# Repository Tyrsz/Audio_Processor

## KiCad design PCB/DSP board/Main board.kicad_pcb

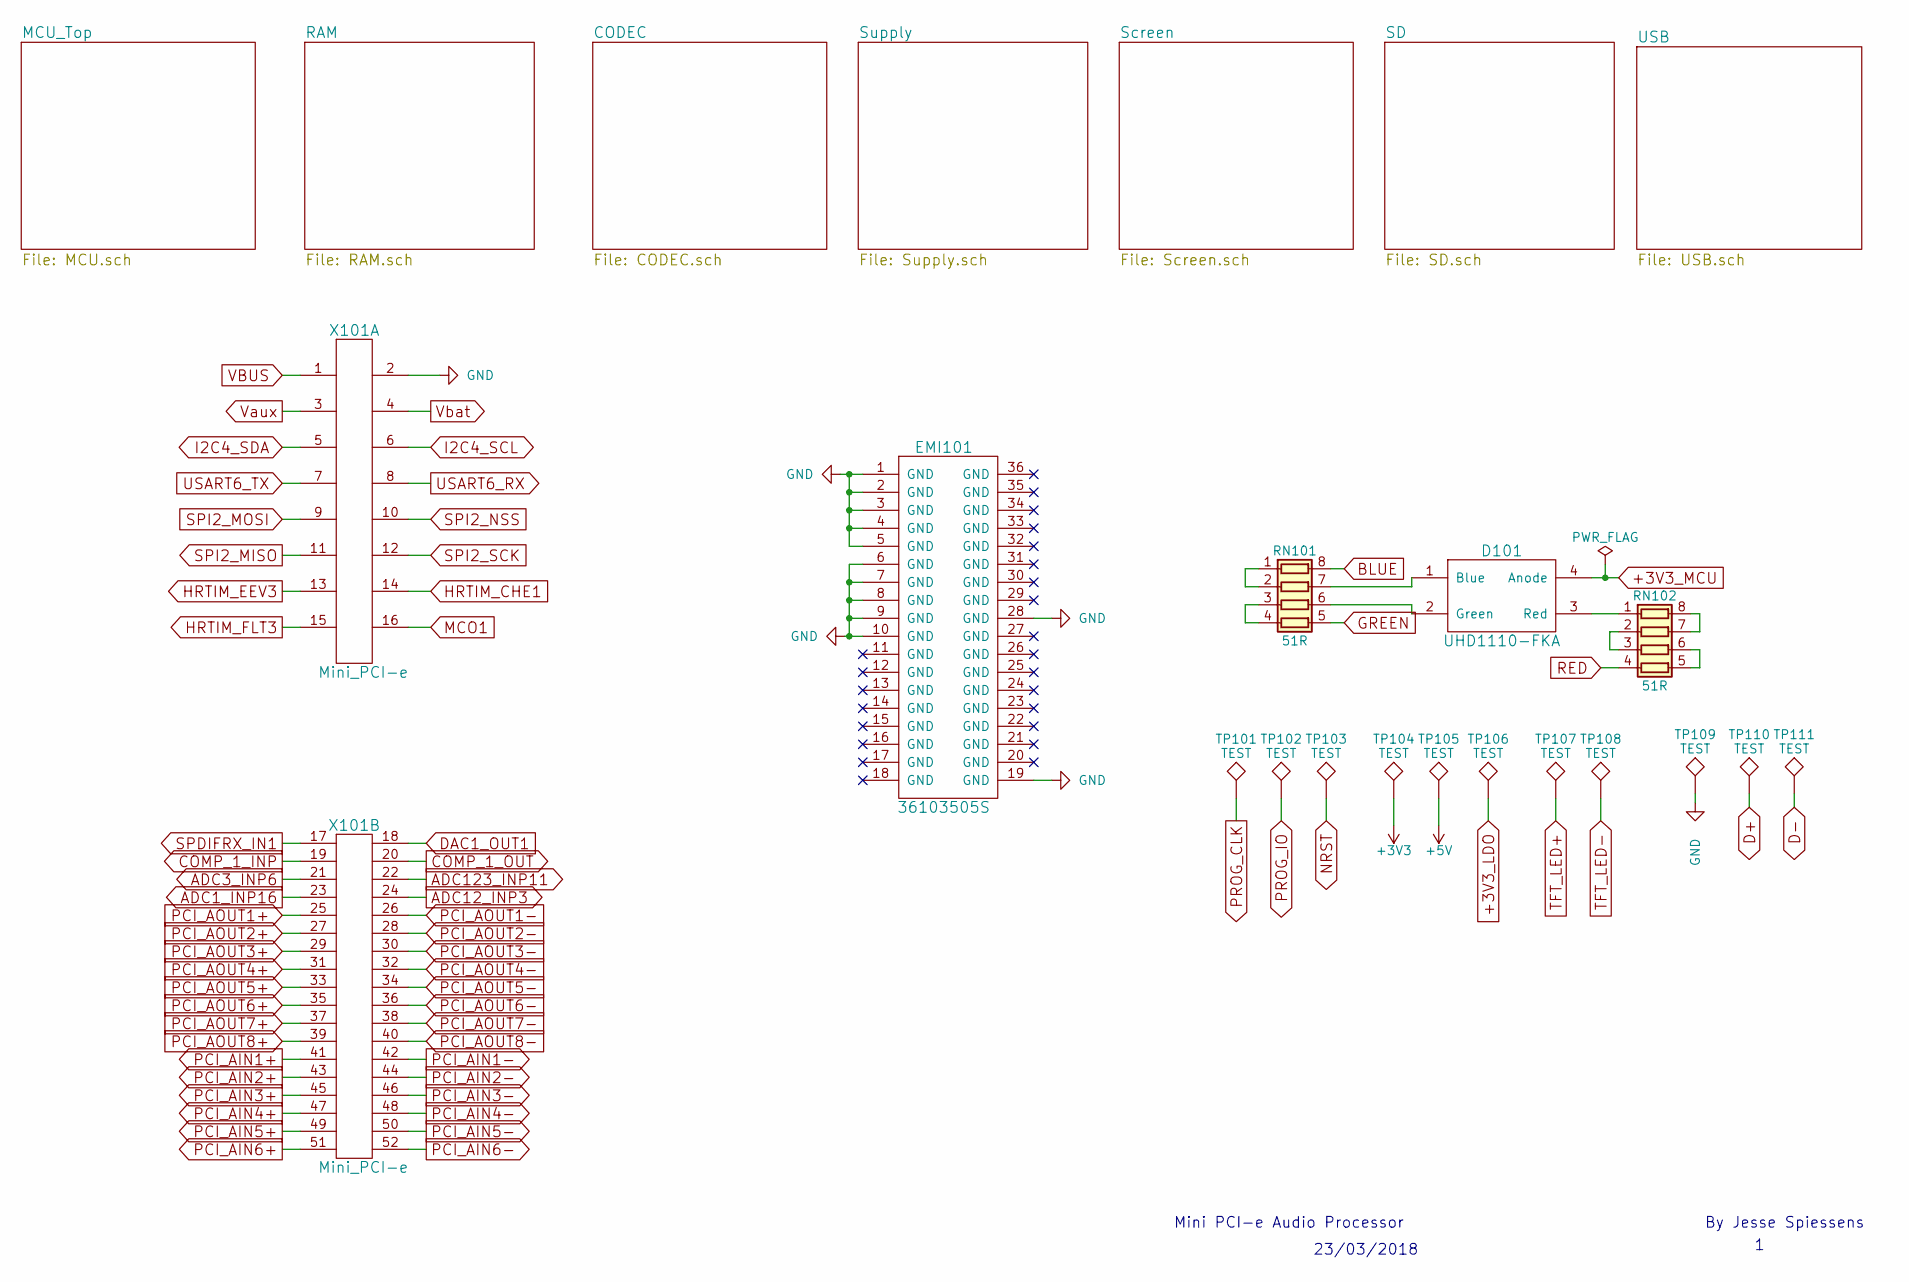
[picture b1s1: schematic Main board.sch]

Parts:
D101: UHD1110-FKA; PLCC-4_1x1mm
EMI101: 36103505S
RN101, RN102: 51R; 0603_RN4
TP101, TP102, TP103, TP104, TP105, TP106, TP107, TP108, TP109, TP110, TP111: TEST; Measurement_Point_Round-SMD-Pad_Small
X101: Mini_PCI-e

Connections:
+3V3: TP104.1; also elsewhere on the board
+3V3_LDO: TP106.1; also elsewhere on the board
+3V3_MCU: D101.4 (Anode); also elsewhere on the board
+5V: TP105.1; also elsewhere on the board
ADC1_INP16: X101.23; also elsewhere on the board
ADC3_INP6: X101.21; also elsewhere on the board
ADC12_INP3: X101.24; also elsewhere on the board
ADC123_INP11: X101.22; also elsewhere on the board
BLUE: RN101.8 (R1.2); also elsewhere on the board
COMP_1_INP: X101.19; also elsewhere on the board
COMP_1_OUT: X101.20; also elsewhere on the board
D+: TP110.1; also elsewhere on the board
D-: TP111.1; also elsewhere on the board
DAC1_OUT1: X101.18; also elsewhere on the board
GND: EMI101.1, EMI101.2, EMI101.3, EMI101.4, EMI101.5, EMI101.6, EMI101.7, EMI101.8, EMI101.9, EMI101.10, EMI101.19, EMI101.28, TP109.1, X101.2; also elsewhere on the board
GREEN: RN101.5 (R4.2); also elsewhere on the board
HRTIM_CHE1: X101.14; also elsewhere on the board
HRTIM_EEV3: X101.13; also elsewhere on the board
HRTIM_FLT3: X101.15; also elsewhere on the board
I2C4_SCL: X101.6; also elsewhere on the board
I2C4_SDA: X101.5; also elsewhere on the board
MCO1: X101.16; also elsewhere on the board
NRST: TP103.1; also elsewhere on the board
unnamed: D101.1 (Blue), RN101.7 (R2.2)
unnamed: D101.2 (Green), RN101.6 (R3.2)
unnamed: D101.3 (Red), RN102.1 (R1.1)
unnamed: RN101.1 (R1.1), RN101.2 (R2.1)
unnamed: RN101.3 (R3.1), RN101.4 (R4.1)
unnamed: RN102.2 (R2.1), RN102.3 (R3.1)
unnamed: RN102.5 (R4.2), RN102.6 (R3.2)
unnamed: RN102.7 (R2.2), RN102.8 (R1.2)
PCI_AIN1+: X101.41; also elsewhere on the board
PCI_AIN1-: X101.42; also elsewhere on the board
PCI_AIN2+: X101.43; also elsewhere on the board
PCI_AIN2-: X101.44; also elsewhere on the board
PCI_AIN3+: X101.45; also elsewhere on the board
PCI_AIN3-: X101.46; also elsewhere on the board
PCI_AIN4+: X101.47; also elsewhere on the board
PCI_AIN4-: X101.48; also elsewhere on the board
PCI_AIN5+: X101.49; also elsewhere on the board
PCI_AIN5-: X101.50; also elsewhere on the board
PCI_AIN6+: X101.51; also elsewhere on the board
PCI_AIN6-: X101.52; also elsewhere on the board
PCI_AOUT1+: X101.25; also elsewhere on the board
PCI_AOUT1-: X101.26; also elsewhere on the board
PCI_AOUT2+: X101.27; also elsewhere on the board
PCI_AOUT2-: X101.28; also elsewhere on the board
PCI_AOUT3+: X101.29; also elsewhere on the board
PCI_AOUT3-: X101.30; also elsewhere on the board
PCI_AOUT4+: X101.31; also elsewhere on the board
PCI_AOUT4-: X101.32; also elsewhere on the board
PCI_AOUT5+: X101.33; also elsewhere on the board
PCI_AOUT5-: X101.34; also elsewhere on the board
PCI_AOUT6+: X101.35; also elsewhere on the board
PCI_AOUT6-: X101.36; also elsewhere on the board
PCI_AOUT7+: X101.37; also elsewhere on the board
PCI_AOUT7-: X101.38; also elsewhere on the board
PCI_AOUT8+: X101.39; also elsewhere on the board
PCI_AOUT8-: X101.40; also elsewhere on the board
PROG_CLK: TP101.1; also elsewhere on the board
PROG_IO: TP102.1; also elsewhere on the board
RED: RN102.4 (R4.1); also elsewhere on the board
SPDIFRX_IN1: X101.17; also elsewhere on the board
SPI2_MISO: X101.11; also elsewhere on the board
SPI2_MOSI: X101.9; also elsewhere on the board
SPI2_NSS: X101.10; also elsewhere on the board
SPI2_SCK: X101.12; also elsewhere on the board
TFT_LED+: TP107.1; also elsewhere on the board
TFT_LED-: TP108.1; also elsewhere on the board
USART6_RX: X101.8; also elsewhere on the board
USART6_TX: X101.7; also elsewhere on the board
VBUS: X101.1; also elsewhere on the board
Vaux: X101.3; also elsewhere on the board
Vbat: X101.4; also elsewhere on the board

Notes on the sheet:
23/03/2018
Mini PCI-e Audio Processor
By Jesse Spiessens

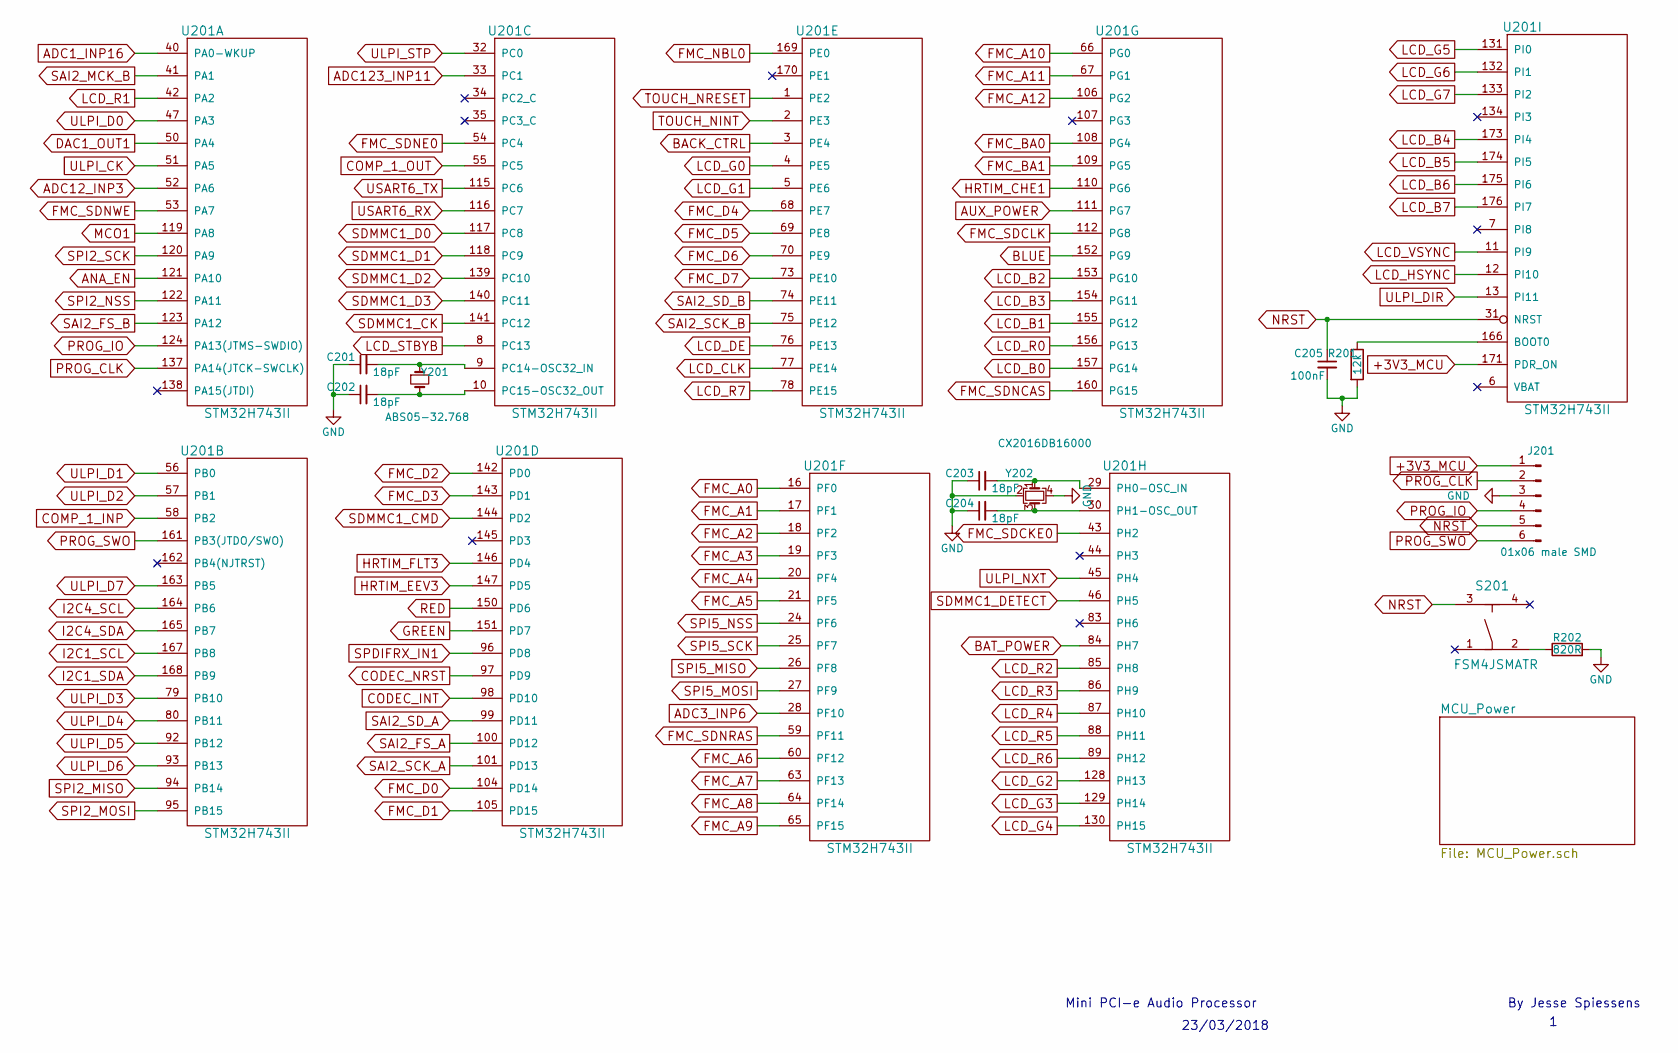
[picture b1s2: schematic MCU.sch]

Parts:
C201, C202, C203, C204: 18pF; C_0603
C205: 100nF; C_0603
J201: 01x06 male SMD; Pin_Header_Straight_1x06_Pitch2.54mm_SMD_Pin1Right
R201: 12k; R_0603
R202: 820R; R_0603
S201: FSM4JSMATR
U201: STM32H743II; LQFP-176_24x24mm_Pitch0.5mm
Y201: ABS05-32.768; Crystal_SMD_MicroCrystal_CM9V-T1A-2pin_1.6x1.0mm
Y202: CX2016DB16000; Crystal_SMD_2016-4pin_2.0x1.6mm

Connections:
+3V3_MCU: J201.1, U201.171 (PDR_ON); also elsewhere on the board
ADC1_INP16: U201.40 (PA0-WKUP); also elsewhere on the board
ADC3_INP6: U201.28 (PF10); also elsewhere on the board
ADC12_INP3: U201.52 (PA6); also elsewhere on the board
ADC123_INP11: U201.33 (PC1); also elsewhere on the board
ANA_EN: U201.121 (PA10); also elsewhere on the board
AUX_POWER: U201.111 (PG7); also elsewhere on the board
BACK_CTRL: U201.3 (PE4); also elsewhere on the board
BAT_POWER: U201.84 (PH7); also elsewhere on the board
BLUE: U201.152 (PG9); also elsewhere on the board
CODEC_INT: U201.98 (PD10); also elsewhere on the board
CODEC_NRST: U201.97 (PD9); also elsewhere on the board
COMP_1_INP: U201.58 (PB2); also elsewhere on the board
COMP_1_OUT: U201.55 (PC5); also elsewhere on the board
DAC1_OUT1: U201.50 (PA4); also elsewhere on the board
FMC_A0: U201.16 (PF0); also elsewhere on the board
FMC_A1: U201.17 (PF1); also elsewhere on the board
FMC_A2: U201.18 (PF2); also elsewhere on the board
FMC_A3: U201.19 (PF3); also elsewhere on the board
FMC_A4: U201.20 (PF4); also elsewhere on the board
FMC_A5: U201.21 (PF5); also elsewhere on the board
FMC_A6: U201.60 (PF12); also elsewhere on the board
FMC_A7: U201.63 (PF13); also elsewhere on the board
FMC_A8: U201.64 (PF14); also elsewhere on the board
FMC_A9: U201.65 (PF15); also elsewhere on the board
FMC_A10: U201.66 (PG0); also elsewhere on the board
FMC_A11: U201.67 (PG1); also elsewhere on the board
FMC_A12: U201.106 (PG2); also elsewhere on the board
FMC_BA0: U201.108 (PG4); also elsewhere on the board
FMC_BA1: U201.109 (PG5); also elsewhere on the board
FMC_D0: U201.104 (PD14); also elsewhere on the board
FMC_D1: U201.105 (PD15); also elsewhere on the board
FMC_D2: U201.142 (PD0); also elsewhere on the board
FMC_D3: U201.143 (PD1); also elsewhere on the board
FMC_D4: U201.68 (PE7); also elsewhere on the board
FMC_D5: U201.69 (PE8); also elsewhere on the board
FMC_D6: U201.70 (PE9); also elsewhere on the board
FMC_D7: U201.73 (PE10); also elsewhere on the board
FMC_NBL0: U201.169 (PE0); also elsewhere on the board
FMC_SDCKE0: U201.43 (PH2); also elsewhere on the board
FMC_SDCLK: U201.112 (PG8); also elsewhere on the board
FMC_SDNCAS: U201.160 (PG15); also elsewhere on the board
FMC_SDNE0: U201.54 (PC4); also elsewhere on the board
FMC_SDNRAS: U201.59 (PF11); also elsewhere on the board
FMC_SDNWE: U201.53 (PA7); also elsewhere on the board
GND: C201.1, C202.1, C203.1, C204.1, C205.2, J201.3, R201.2, R202.2, Y202.2, Y202.4; also elsewhere on the board
GREEN: U201.151 (PD7); also elsewhere on the board
HRTIM_CHE1: U201.110 (PG6); also elsewhere on the board
HRTIM_EEV3: U201.147 (PD5); also elsewhere on the board
HRTIM_FLT3: U201.146 (PD4); also elsewhere on the board
I2C1_SCL: U201.167 (PB8); also elsewhere on the board
I2C1_SDA: U201.168 (PB9); also elsewhere on the board
I2C4_SCL: U201.164 (PB6); also elsewhere on the board
I2C4_SDA: U201.165 (PB7); also elsewhere on the board
LCD_B0: U201.157 (PG14); also elsewhere on the board
LCD_B1: U201.155 (PG12); also elsewhere on the board
LCD_B2: U201.153 (PG10); also elsewhere on the board
LCD_B3: U201.154 (PG11); also elsewhere on the board
LCD_B4: U201.173 (PI4); also elsewhere on the board
LCD_B5: U201.174 (PI5); also elsewhere on the board
LCD_B6: U201.175 (PI6); also elsewhere on the board
LCD_B7: U201.176 (PI7); also elsewhere on the board
LCD_CLK: U201.77 (PE14); also elsewhere on the board
LCD_DE: U201.76 (PE13); also elsewhere on the board
LCD_G0: U201.4 (PE5); also elsewhere on the board
LCD_G1: U201.5 (PE6); also elsewhere on the board
LCD_G2: U201.128 (PH13); also elsewhere on the board
LCD_G3: U201.129 (PH14); also elsewhere on the board
LCD_G4: U201.130 (PH15); also elsewhere on the board
LCD_G5: U201.131 (PI0); also elsewhere on the board
LCD_G6: U201.132 (PI1); also elsewhere on the board
LCD_G7: U201.133 (PI2); also elsewhere on the board
LCD_HSYNC: U201.12 (PI10); also elsewhere on the board
LCD_R0: U201.156 (PG13); also elsewhere on the board
LCD_R1: U201.42 (PA2); also elsewhere on the board
LCD_R2: U201.85 (PH8); also elsewhere on the board
LCD_R3: U201.86 (PH9); also elsewhere on the board
LCD_R4: U201.87 (PH10); also elsewhere on the board
LCD_R5: U201.88 (PH11); also elsewhere on the board
LCD_R6: U201.89 (PH12); also elsewhere on the board
LCD_R7: U201.78 (PE15); also elsewhere on the board
LCD_STBYB: U201.8 (PC13); also elsewhere on the board
LCD_VSYNC: U201.11 (PI9); also elsewhere on the board
MCO1: U201.119 (PA8); also elsewhere on the board
NRST: C205.1, J201.5, S201.3, U201.31 (NRST); also elsewhere on the board
unnamed: C201.2, U201.9 (PC14-OSC32_IN), Y201.1
unnamed: C202.2, U201.10 (PC15-OSC32_OUT), Y201.2
unnamed: C203.2, U201.29 (PH0-OSC_IN), Y202.1
unnamed: C204.2, U201.30 (PH1-OSC_OUT), Y202.3
unnamed: R201.1, U201.166 (BOOT0)
unnamed: R202.1, S201.2
PROG_CLK: J201.2, U201.137 (PA14(JTCK-SWCLK)); also elsewhere on the board
PROG_IO: J201.4, U201.124 (PA13(JTMS-SWDIO)); also elsewhere on the board
PROG_SWO: J201.6, U201.161 (PB3(JTDO/SWO))
RED: U201.150 (PD6); also elsewhere on the board
SAI2_FS_A: U201.100 (PD12); also elsewhere on the board
SAI2_FS_B: U201.123 (PA12); also elsewhere on the board
SAI2_MCK_B: U201.41 (PA1); also elsewhere on the board
SAI2_SCK_A: U201.101 (PD13); also elsewhere on the board
SAI2_SCK_B: U201.75 (PE12); also elsewhere on the board
SAI2_SD_A: U201.99 (PD11); also elsewhere on the board
SAI2_SD_B: U201.74 (PE11); also elsewhere on the board
SDMMC1_CK: U201.141 (PC12); also elsewhere on the board
SDMMC1_CMD: U201.144 (PD2); also elsewhere on the board
SDMMC1_D0: U201.117 (PC8); also elsewhere on the board
SDMMC1_D1: U201.118 (PC9); also elsewhere on the board
SDMMC1_D2: U201.139 (PC10); also elsewhere on the board
SDMMC1_D3: U201.140 (PC11); also elsewhere on the board
SDMMC1_DETECT: U201.46 (PH5); also elsewhere on the board
SPDIFRX_IN1: U201.96 (PD8); also elsewhere on the board
SPI2_MISO: U201.94 (PB14); also elsewhere on the board
SPI2_MOSI: U201.95 (PB15); also elsewhere on the board
SPI2_NSS: U201.122 (PA11); also elsewhere on the board
SPI2_SCK: U201.120 (PA9); also elsewhere on the board
SPI5_MISO: U201.26 (PF8); also elsewhere on the board
SPI5_MOSI: U201.27 (PF9); also elsewhere on the board
SPI5_NSS: U201.24 (PF6); also elsewhere on the board
SPI5_SCK: U201.25 (PF7); also elsewhere on the board
TOUCH_NINT: U201.2 (PE3); also elsewhere on the board
TOUCH_NRESET: U201.1 (PE2); also elsewhere on the board
ULPI_CK: U201.51 (PA5); also elsewhere on the board
ULPI_D0: U201.47 (PA3); also elsewhere on the board
ULPI_D1: U201.56 (PB0); also elsewhere on the board
ULPI_D2: U201.57 (PB1); also elsewhere on the board
ULPI_D3: U201.79 (PB10); also elsewhere on the board
ULPI_D4: U201.80 (PB11); also elsewhere on the board
ULPI_D5: U201.92 (PB12); also elsewhere on the board
ULPI_D6: U201.93 (PB13); also elsewhere on the board
ULPI_D7: U201.163 (PB5); also elsewhere on the board
ULPI_DIR: U201.13 (PI11); also elsewhere on the board
ULPI_NXT: U201.45 (PH4); also elsewhere on the board
ULPI_STP: U201.32 (PC0); also elsewhere on the board
USART6_RX: U201.116 (PC7); also elsewhere on the board
USART6_TX: U201.115 (PC6); also elsewhere on the board

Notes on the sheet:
23/03/2018
Mini PCI-e Audio Processor
By Jesse Spiessens

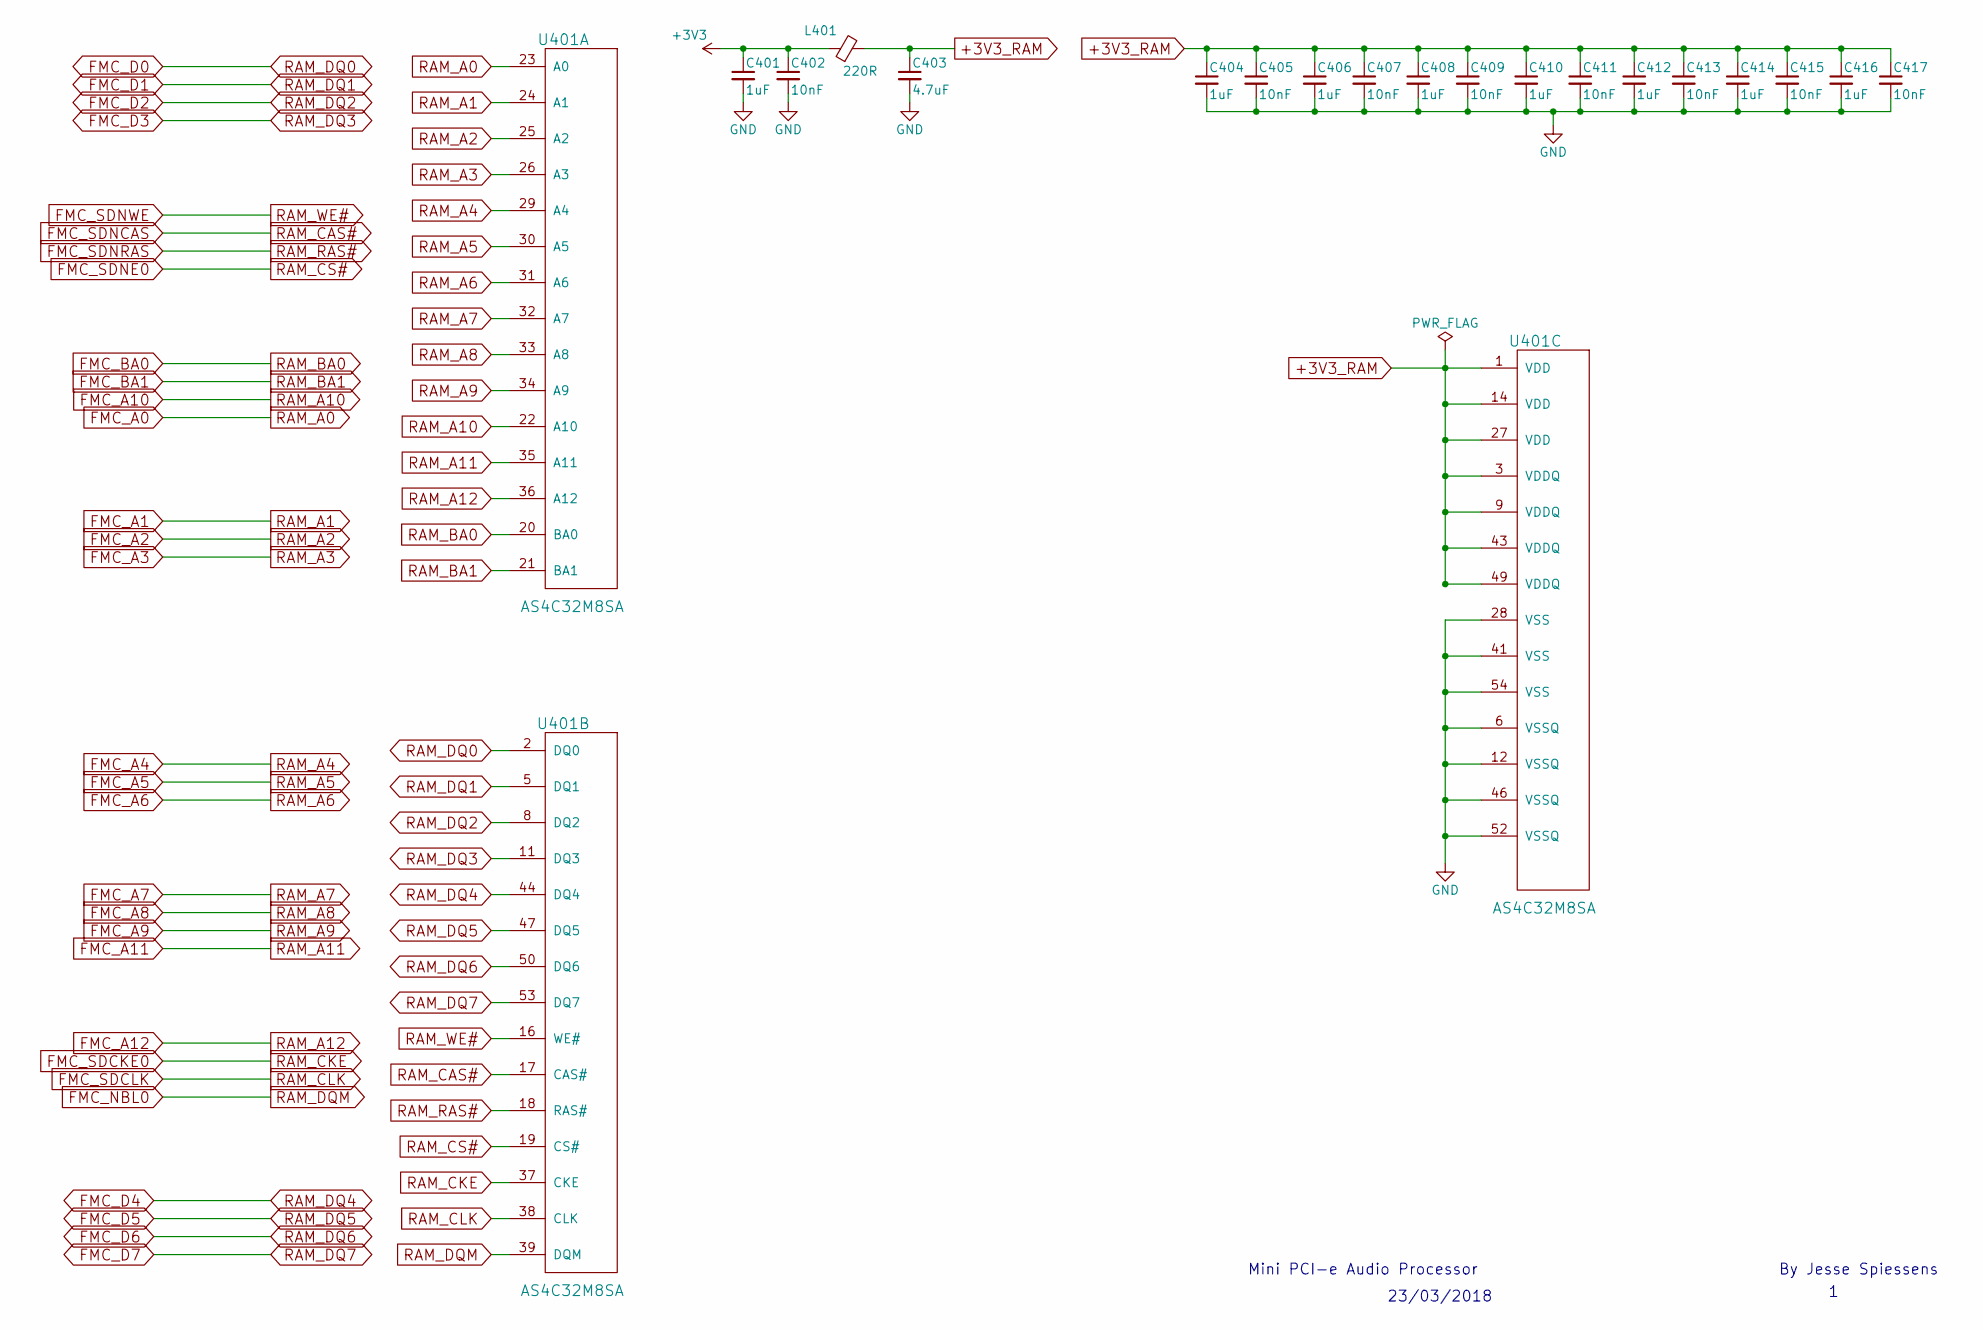
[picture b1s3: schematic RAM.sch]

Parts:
C401, C404, C406, C408, C410, C412, C414, C416: 1uF; C_0603
C402, C405, C407, C409, C411, C413, C415, C417: 10nF; C_0603
C403: 4.7uF; C_0805
L401: 220R; L_0603
U401: AS4C32M8SA; TSSOP-54_P-0.8mm

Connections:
+3V3: C401.1, C402.1, L401.1; also elsewhere on the board
+3V3_RAM: C403.1, C404.1, C405.1, C406.1, C407.1, C408.1, C409.1, C410.1, C411.1, C412.1, C413.1, C414.1, C415.1, C416.1, C417.1, L401.2, U401.1 (VDD), U401.3 (VDDQ), U401.9 (VDDQ), U401.14 (VDD), U401.27 (VDD), U401.43 (VDDQ), U401.49 (VDDQ)
FMC_A0: U401.23 (A0); also elsewhere on the board
FMC_A1: U401.24 (A1); also elsewhere on the board
FMC_A2: U401.25 (A2); also elsewhere on the board
FMC_A3: U401.26 (A3); also elsewhere on the board
FMC_A4: U401.29 (A4); also elsewhere on the board
FMC_A5: U401.30 (A5); also elsewhere on the board
FMC_A6: U401.31 (A6); also elsewhere on the board
FMC_A7: U401.32 (A7); also elsewhere on the board
FMC_A8: U401.33 (A8); also elsewhere on the board
FMC_A9: U401.34 (A9); also elsewhere on the board
FMC_A10: U401.22 (A10); also elsewhere on the board
FMC_A11: U401.35 (A11); also elsewhere on the board
FMC_A12: U401.36 (A12); also elsewhere on the board
FMC_BA0: U401.20 (BA0); also elsewhere on the board
FMC_BA1: U401.21 (BA1); also elsewhere on the board
FMC_D0: U401.2 (DQ0); also elsewhere on the board
FMC_D1: U401.5 (DQ1); also elsewhere on the board
FMC_D2: U401.8 (DQ2); also elsewhere on the board
FMC_D3: U401.11 (DQ3); also elsewhere on the board
FMC_D4: U401.44 (DQ4); also elsewhere on the board
FMC_D5: U401.47 (DQ5); also elsewhere on the board
FMC_D6: U401.50 (DQ6); also elsewhere on the board
FMC_D7: U401.53 (DQ7); also elsewhere on the board
FMC_NBL0: U401.39 (DQM); also elsewhere on the board
FMC_SDCKE0: U401.37 (CKE); also elsewhere on the board
FMC_SDCLK: U401.38 (CLK); also elsewhere on the board
FMC_SDNCAS: U401.17 (CAS#); also elsewhere on the board
FMC_SDNE0: U401.19 (CS#); also elsewhere on the board
FMC_SDNRAS: U401.18 (RAS#); also elsewhere on the board
FMC_SDNWE: U401.16 (WE#); also elsewhere on the board
GND: C401.2, C402.2, C403.2, C404.2, C405.2, C406.2, C407.2, C408.2, C409.2, C410.2, C411.2, C412.2, C413.2, C414.2, C415.2, C416.2, C417.2, U401.6 (VSSQ), U401.12 (VSSQ), U401.28 (VSS), U401.41 (VSS), U401.46 (VSSQ), U401.52 (VSSQ), U401.54 (VSS); also elsewhere on the board

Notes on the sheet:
23/03/2018
Mini PCI-e Audio Processor
By Jesse Spiessens

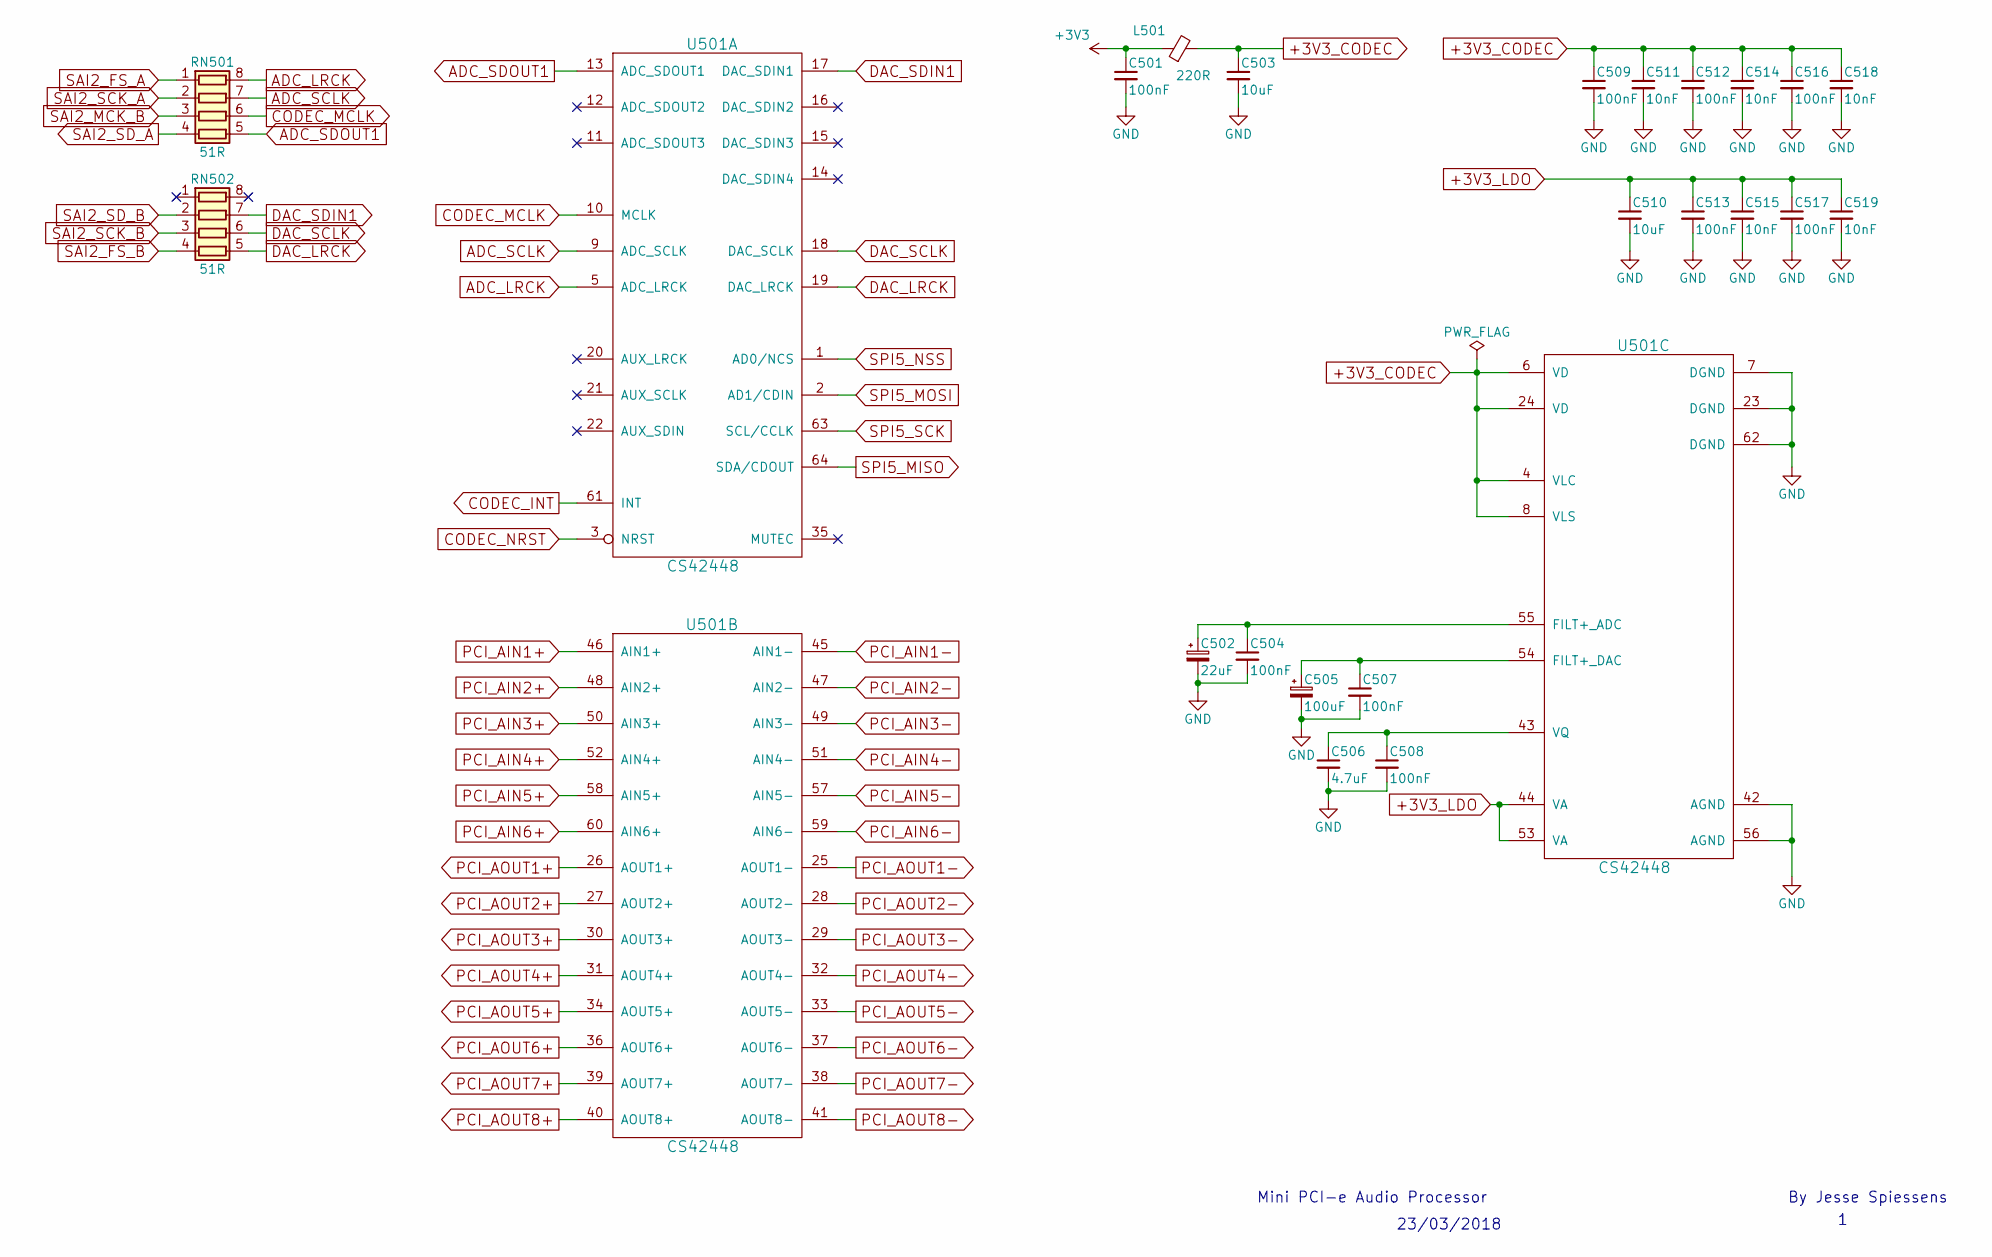
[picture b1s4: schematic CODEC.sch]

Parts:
C501, C504, C507, C508, C509, C512, C513, C516, C517: 100nF; C_0603
C502: 22uF; CP_Tantalum_Case-A_EIA-3216-18_Reflow
C503, C510: 10uF; C_0805
C505: 100uF; CP_Tantalum_Case-B_EIA-3528-21_Reflow
C506: 4.7uF; C_0805
C511, C514, C515, C518, C519: 10nF; C_0603
L501: 220R; L_0603
RN501, RN502: 51R; 0603_RN4
U501: CS42448; LQFP-64_10x10mm_Pitch0.5mm

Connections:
+3V3: C501.1, L501.1; also elsewhere on the board
+3V3_CODEC: C503.1, C509.1, C511.1, C512.1, C514.1, C516.1, C518.1, L501.2, U501.4 (VLC), U501.6 (VD), U501.8 (VLS), U501.24 (VD)
+3V3_LDO: C510.1, C513.1, C515.1, C517.1, C519.1, U501.44 (VA), U501.53 (VA); also elsewhere on the board
ADC_LRCK: RN501.8 (R1.2), U501.5 (ADC_LRCK)
ADC_SCLK: RN501.7 (R2.2), U501.9 (ADC_SCLK)
ADC_SDOUT1: RN501.5 (R4.2), U501.13 (ADC_SDOUT1)
CODEC_INT: U501.61 (INT); also elsewhere on the board
CODEC_MCLK: RN501.6 (R3.2), U501.10 (MCLK)
CODEC_NRST: U501.3 (NRST); also elsewhere on the board
DAC_LRCK: RN502.5 (R4.2), U501.19 (DAC_LRCK)
DAC_SCLK: RN502.6 (R3.2), U501.18 (DAC_SCLK)
DAC_SDIN1: RN502.7 (R2.2), U501.17 (DAC_SDIN1)
GND: C501.2, C502.2, C503.2, C504.2, C505.2, C506.2, C507.2, C508.2, C509.2, C510.2, C511.2, C512.2, C513.2, C514.2, C515.2, C516.2, C517.2, C518.2, C519.2, U501.7 (DGND), U501.23 (DGND), U501.42 (AGND), U501.56 (AGND), U501.62 (DGND); also elsewhere on the board
unnamed: C502.1, C504.1, U501.55 (FILT+_ADC)
unnamed: C505.1, C507.1, U501.54 (FILT+_DAC)
unnamed: C506.1, C508.1, U501.43 (VQ)
PCI_AIN1+: U501.46 (AIN1+); also elsewhere on the board
PCI_AIN1-: U501.45 (AIN1-); also elsewhere on the board
PCI_AIN2+: U501.48 (AIN2+); also elsewhere on the board
PCI_AIN2-: U501.47 (AIN2-); also elsewhere on the board
PCI_AIN3+: U501.50 (AIN3+); also elsewhere on the board
PCI_AIN3-: U501.49 (AIN3-); also elsewhere on the board
PCI_AIN4+: U501.52 (AIN4+); also elsewhere on the board
PCI_AIN4-: U501.51 (AIN4-); also elsewhere on the board
PCI_AIN5+: U501.58 (AIN5+); also elsewhere on the board
PCI_AIN5-: U501.57 (AIN5-); also elsewhere on the board
PCI_AIN6+: U501.60 (AIN6+); also elsewhere on the board
PCI_AIN6-: U501.59 (AIN6-); also elsewhere on the board
PCI_AOUT1+: U501.26 (AOUT1+); also elsewhere on the board
PCI_AOUT1-: U501.25 (AOUT1-); also elsewhere on the board
PCI_AOUT2+: U501.27 (AOUT2+); also elsewhere on the board
PCI_AOUT2-: U501.28 (AOUT2-); also elsewhere on the board
PCI_AOUT3+: U501.30 (AOUT3+); also elsewhere on the board
PCI_AOUT3-: U501.29 (AOUT3-); also elsewhere on the board
PCI_AOUT4+: U501.31 (AOUT4+); also elsewhere on the board
PCI_AOUT4-: U501.32 (AOUT4-); also elsewhere on the board
PCI_AOUT5+: U501.34 (AOUT5+); also elsewhere on the board
PCI_AOUT5-: U501.33 (AOUT5-); also elsewhere on the board
PCI_AOUT6+: U501.36 (AOUT6+); also elsewhere on the board
PCI_AOUT6-: U501.37 (AOUT6-); also elsewhere on the board
PCI_AOUT7+: U501.39 (AOUT7+); also elsewhere on the board
PCI_AOUT7-: U501.38 (AOUT7-); also elsewhere on the board
PCI_AOUT8+: U501.40 (AOUT8+); also elsewhere on the board
PCI_AOUT8-: U501.41 (AOUT8-); also elsewhere on the board
SAI2_FS_A: RN501.1 (R1.1); also elsewhere on the board
SAI2_FS_B: RN502.4 (R4.1); also elsewhere on the board
SAI2_MCK_B: RN501.3 (R3.1); also elsewhere on the board
SAI2_SCK_A: RN501.2 (R2.1); also elsewhere on the board
SAI2_SCK_B: RN502.3 (R3.1); also elsewhere on the board
SAI2_SD_A: RN501.4 (R4.1); also elsewhere on the board
SAI2_SD_B: RN502.2 (R2.1); also elsewhere on the board
SPI5_MISO: U501.64 (SDA/CDOUT); also elsewhere on the board
SPI5_MOSI: U501.2 (AD1/CDIN); also elsewhere on the board
SPI5_NSS: U501.1 (AD0/NCS); also elsewhere on the board
SPI5_SCK: U501.63 (SCL/CCLK); also elsewhere on the board

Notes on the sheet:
23/03/2018
Mini PCI-e Audio Processor
By Jesse Spiessens
